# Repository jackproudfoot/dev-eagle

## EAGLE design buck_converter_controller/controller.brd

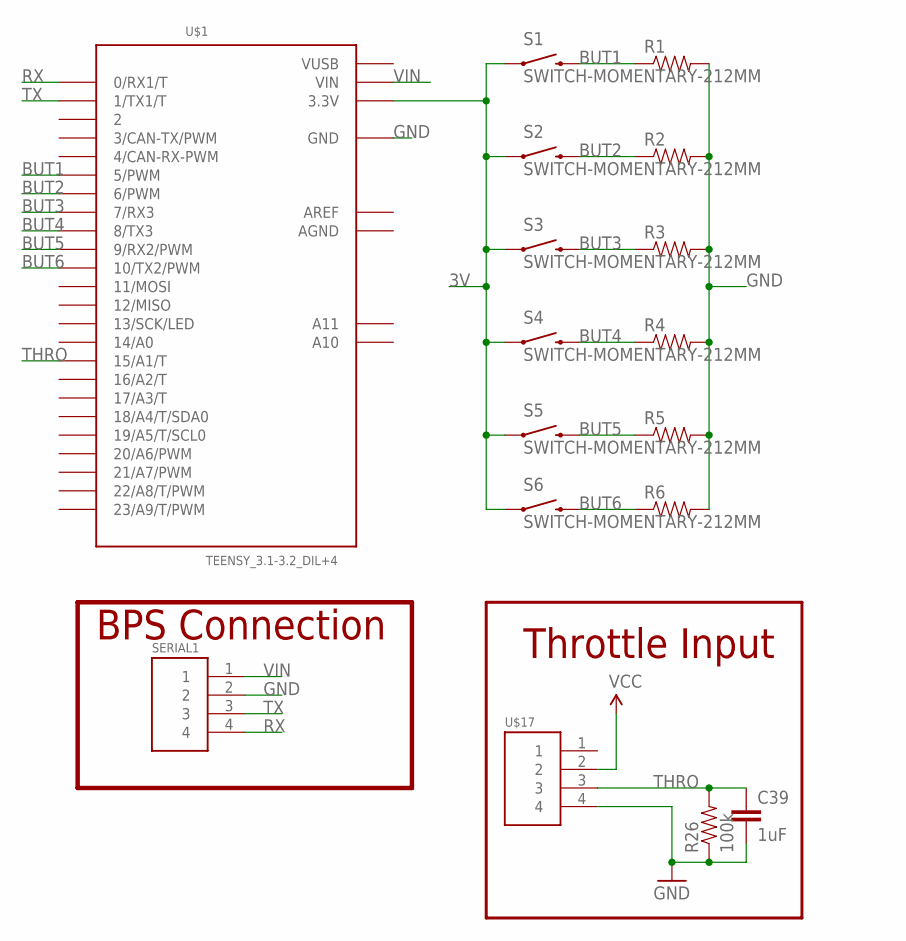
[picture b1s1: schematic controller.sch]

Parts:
C39: 1uF; 0603-CAP
R1, R2, R3, R4, R5, R6: RESISTOR0603-RES; 0603-RES
R26: 100k; 0603-RES
S1, S2, S3, S4, S5, S6: SWITCH-MOMENTARY-212MM; TACTILE-PTH-12MM
SERIAL1: HEADER4VALULOK; 4PINVALULOK
U$1: TEENSY_3.1-3.2_DIL+4; TEENSY_3.0-3.2&LC_DIL+4
U$17: HEADER4VALULOK; 4PINVALULOK

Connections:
3V: S1.1, S2.1, S3.1, S4.1, S5.1, S6.1, U$1.3.3V, U$17.2
AGND: U$1.AGND
AREF: U$1.AREF
BUT1: R1.1, S1.3 (2), U$1.5 (5/PWM)
BUT2: R2.1, S2.3 (2), U$1.6 (6/PWM)
BUT3: R3.1, S3.3 (2), U$1.7 (7/RX3)
BUT4: R4.1, S4.3 (2), U$1.8 (8/TX3)
BUT5: R5.1, S5.3 (2), U$1.9 (9/RX2/PWM)
BUT6: R6.1, S6.3 (2), U$1.10 (10/TX2/PWM)
GND: C39.2, R1.2, R2.2, R3.2, R4.2, R5.2, R6.2, R26.1, SERIAL1.2, U$1.GND, U$17.4
RX: SERIAL1.4, U$1.0 (0/RX1/T)
THRO: C39.1, R26.2, U$1.15/A1 (15/A1/T), U$17.3
TX: SERIAL1.3, U$1.1 (1/TX1/T)
VIN: SERIAL1.1, U$1.VIN
VUSB: U$1.VUSB

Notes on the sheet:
BPS Connection
Throttle Input

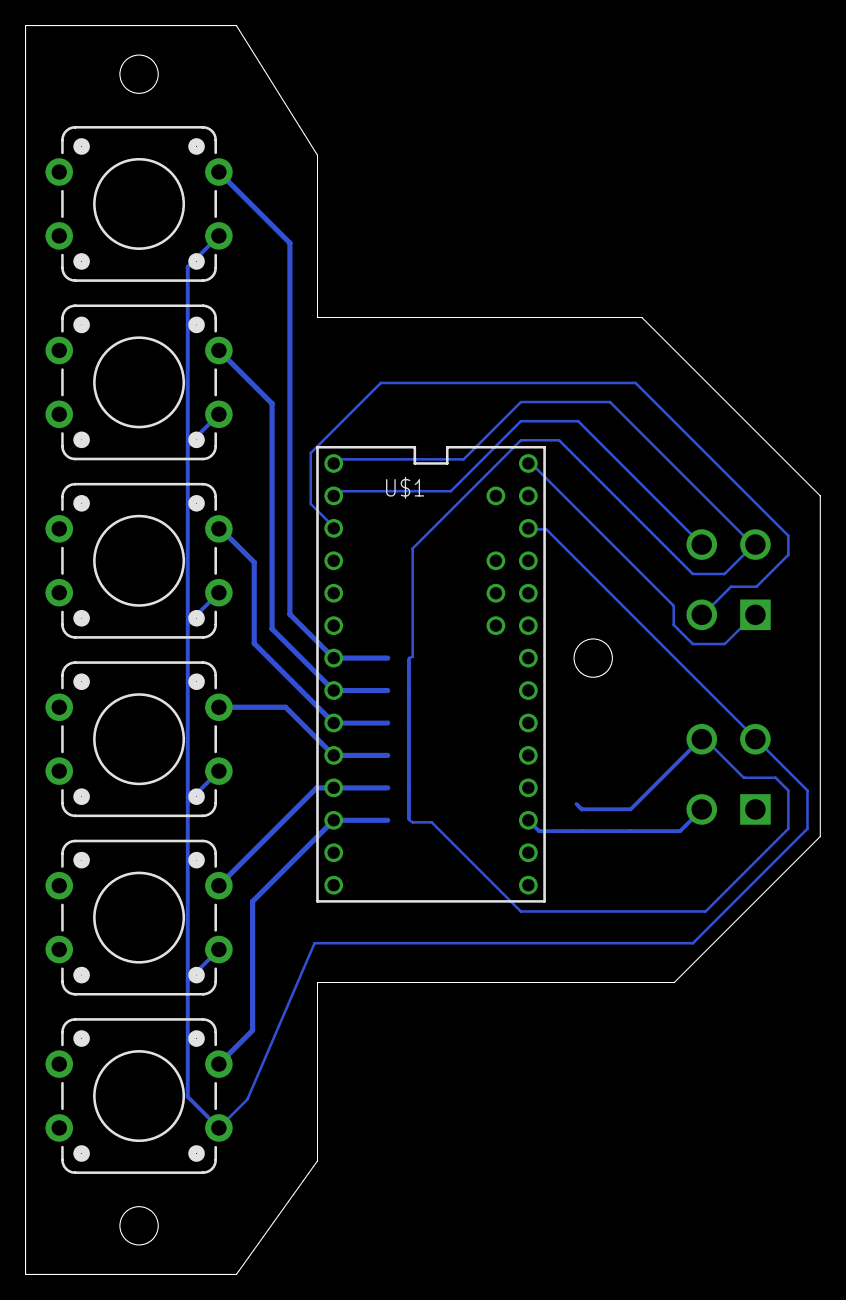
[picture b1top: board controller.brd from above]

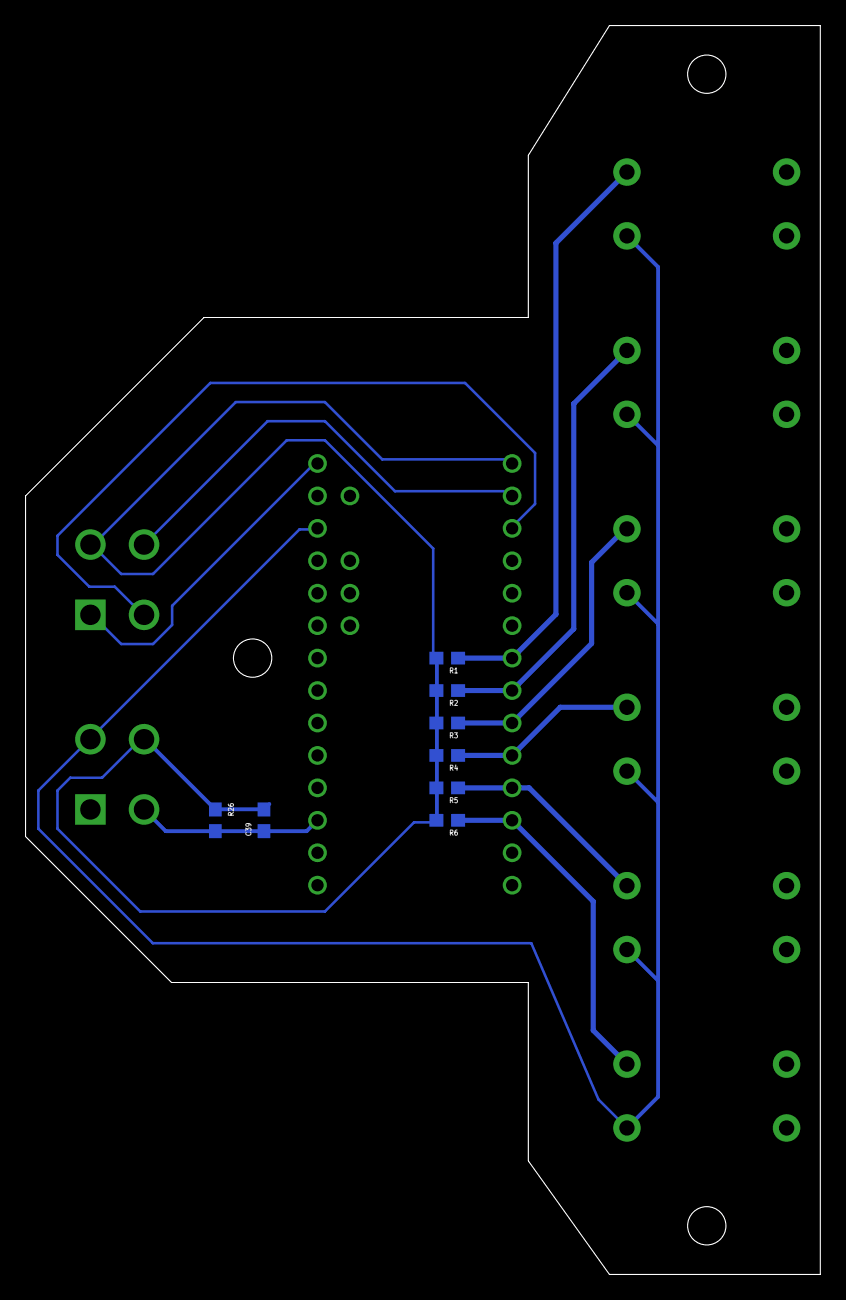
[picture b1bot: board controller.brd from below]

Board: 2 copper layers, 62.2 x 97.8 mm, 17 parts (8 on the bottom side), 12 nets.

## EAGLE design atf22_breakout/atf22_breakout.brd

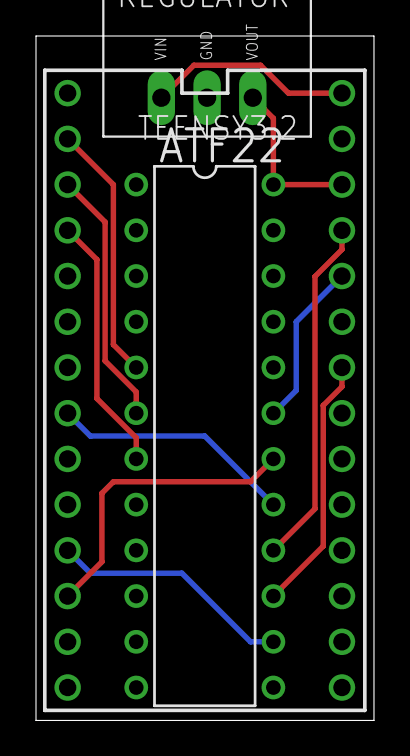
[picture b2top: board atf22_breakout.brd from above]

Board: 2 copper layers, 18.8 x 38.0 mm, 4 parts (1 on the bottom side), 12 nets.

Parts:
ATF22: ATF22; PDIP-T24
REGULATOR: V78W
TEENSY3.2: TEENSY_3.1-3.2_DIL; TEENSY_3.0-3.2&LC_DIL
U$1: DEV

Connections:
3.3V: ATF22.24, REGULATOR.OUT, TEENSY3.2.3.3V
ENC_A: ATF22.5, TEENSY3.2.0
ENC_B: ATF22.6, TEENSY3.2.1
ENC_C: ATF22.7, TEENSY3.2.2
GND: ATF22.12, REGULATOR.GND, TEENSY3.2.GND
INH_A: ATF22.14, TEENSY3.2.9
INH_B: ATF22.15, TEENSY3.2.20/A6
INH_C: ATF22.16, TEENSY3.2.23/A9
INL_A: ATF22.17, TEENSY3.2.6
INL_B: ATF22.18, TEENSY3.2.10
INL_C: ATF22.19, TEENSY3.2.22/A8
VIN: REGULATOR.IN, TEENSY3.2.VIN

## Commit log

2019-03-06 Fixed ATF22 Breakout
    Moved voltage regulator so it fits on the board.
2019-03-22 Added controller board for buck converter

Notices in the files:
parts and their libraries:
SparkFun-Passives: Licensing: Creative Commons ShareAlike 4.0 International - https://creativecommons.org/licenses/by-sa/4.0
